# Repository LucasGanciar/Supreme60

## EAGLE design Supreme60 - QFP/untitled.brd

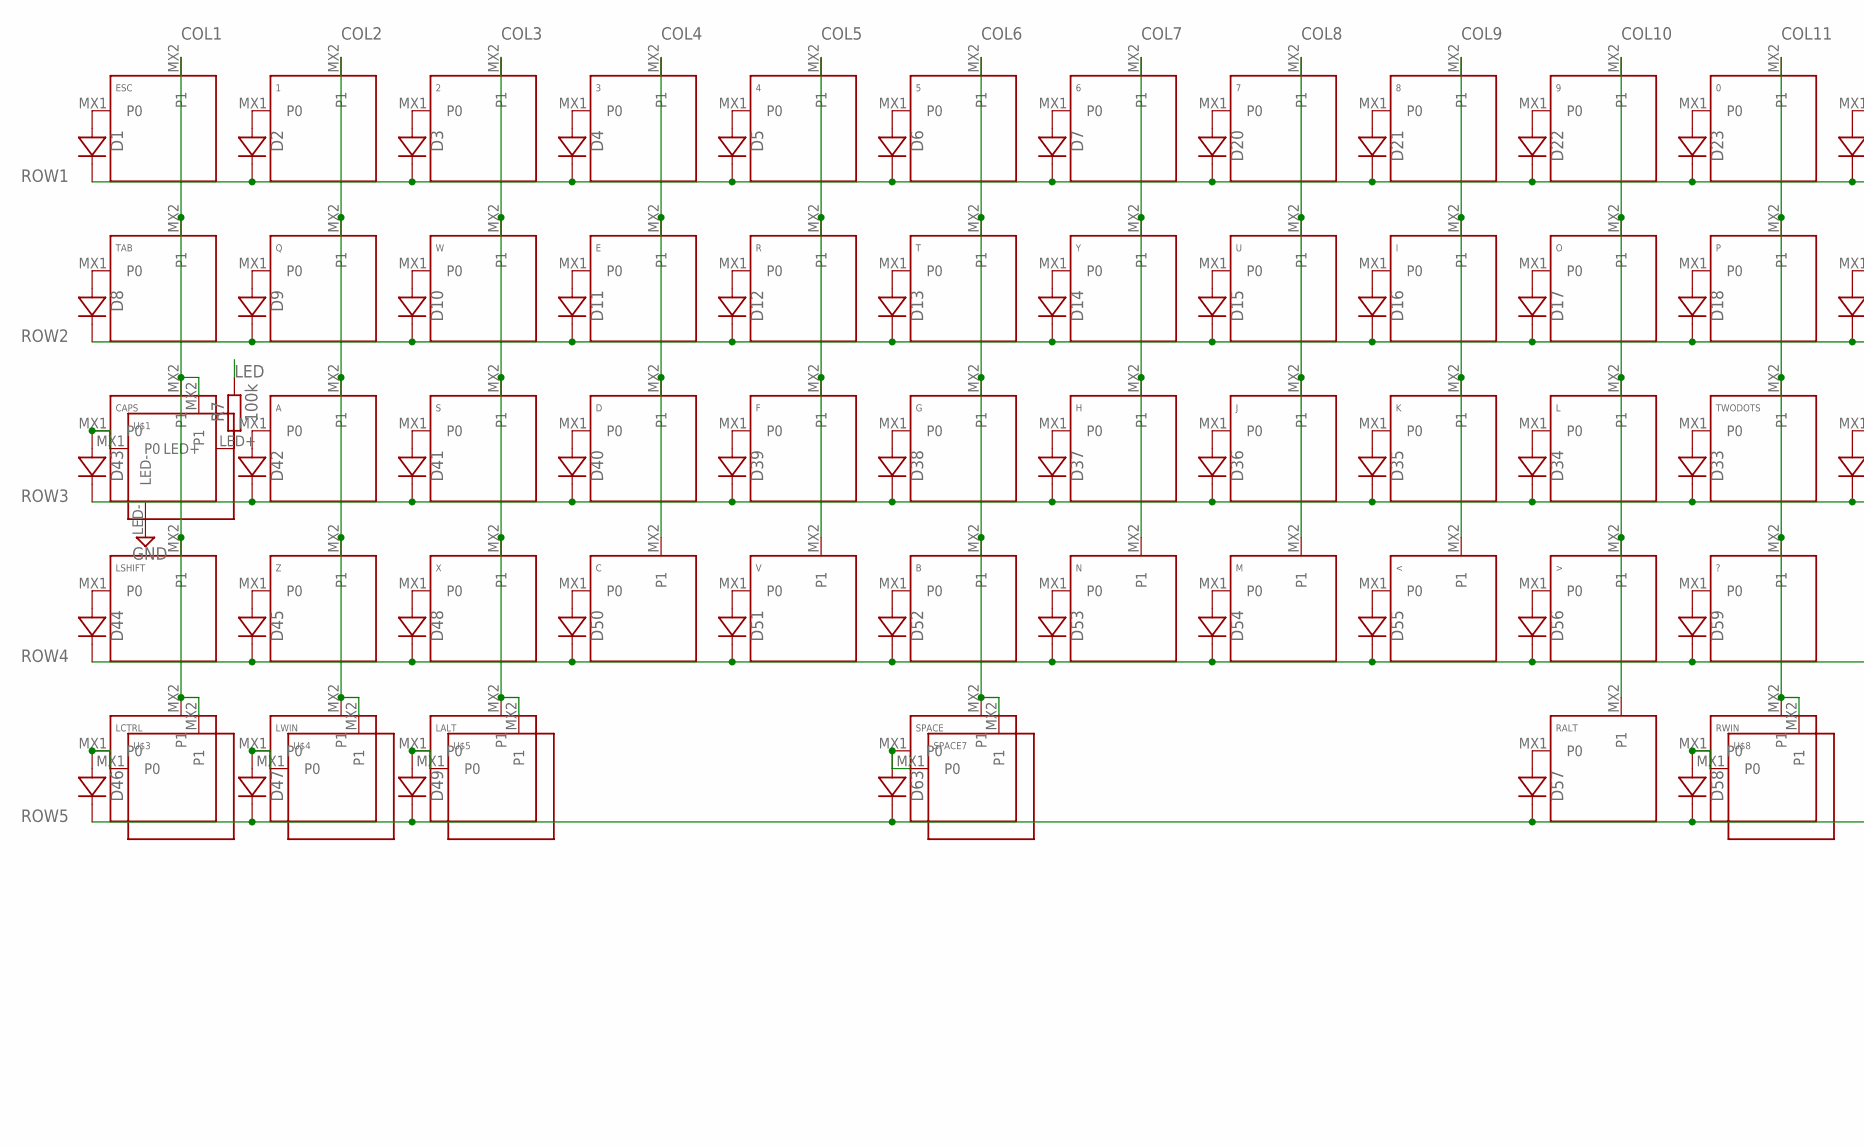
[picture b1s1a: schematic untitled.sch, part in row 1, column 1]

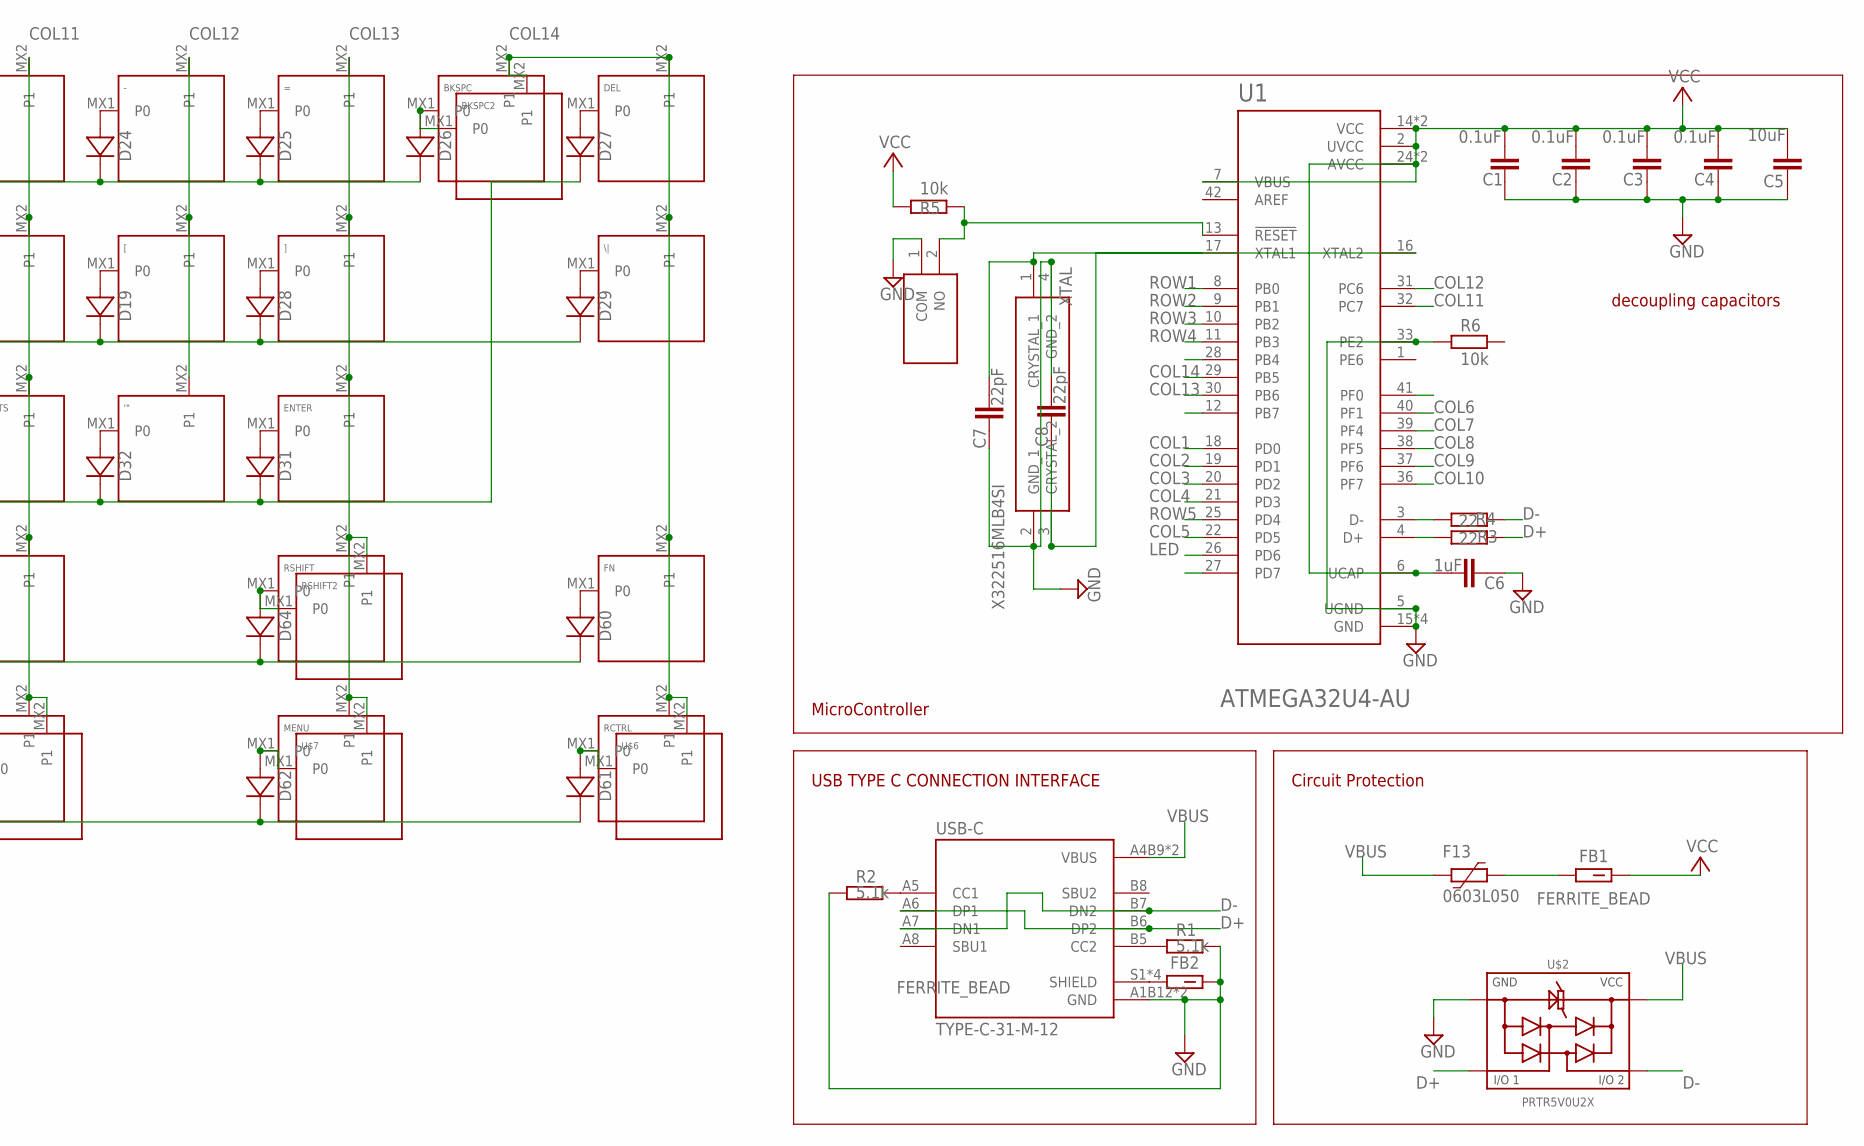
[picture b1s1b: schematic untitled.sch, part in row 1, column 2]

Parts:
0, 1, 2, 3, 4, 5, 6, 7, 8, 9: KEYSWITCH-PLAIN-MX-1U; MX-1U
'": KEYSWITCH-PLAIN-MX-1U; MX-1U
-: KEYSWITCH-PLAIN-MX-1U; MX-1U
<: KEYSWITCH-PLAIN-MX-1U; MX-1U
=: KEYSWITCH-PLAIN-MX-1U; MX-1U
>: KEYSWITCH-PLAIN-MX-1U; MX-1U
?: KEYSWITCH-PLAIN-MX-1U; MX-1U
A: KEYSWITCH-PLAIN-MX-1U; MX-1U
B: KEYSWITCH-PLAIN-MX-1U; MX-1U
BKSPC: KEYSWITCH-PLAIN-MX-1U; MX-1U
BKSPC2: KEYSWITCH-PLAIN-MX-2U; MX-2U
C: KEYSWITCH-PLAIN-MX-1U; MX-1U
C1, C2, C3, C4: 0.1uF; C0603
C5: 10uF; C0603
C6: 1uF; C0603
C7, C8: 22pF; C0603
CAPS: KEYSWITCH-LED-MX-1U-LED; MX-1U-LED
D: KEYSWITCH-PLAIN-MX-1U; MX-1U
D1, D2, D3, D4, D5, D6, D7, D8, D9, D10, D11, D12, D13, D14, D15, D16, D17, D18, D19, D20, D21, D22, D23, D24, D25, D26, D27, D28, D29, D31, D32, D33, D34, D35, D36, D37, D38, D39, D40, D41, D42, D43, D44, D45, D46, D47, D48, D49, D50, D51, D52, D53, D54, D55, D56, D57, D58, D59, D60, D61, D62, D63, D64: DIODE-SOD-123; SOD-123
DEL: KEYSWITCH-PLAIN-MX-1U; MX-1U
E: KEYSWITCH-PLAIN-MX-1U; MX-1U
ENTER: KEYSWITCH-PLAIN-MX-2U; MX-2U
ESC: KEYSWITCH-PLAIN-MX-1U; MX-1U
F: KEYSWITCH-PLAIN-MX-1U; MX-1U
F13: 0603L050; 0603L
FB1, FB2: FERRITE_BEAD; BEADC1608X95N
FN: KEYSWITCH-PLAIN-MX-1U; MX-1U
G: KEYSWITCH-PLAIN-MX-1U; MX-1U
H: KEYSWITCH-PLAIN-MX-1U; MX-1U
I: KEYSWITCH-PLAIN-MX-1U; MX-1U
J: KEYSWITCH-PLAIN-MX-1U; MX-1U
K: KEYSWITCH-PLAIN-MX-1U; MX-1U
L: KEYSWITCH-PLAIN-MX-1U; MX-1U
LALT: KEYSWITCH-PLAIN-MX-1U; MX-1U
LCTRL: KEYSWITCH-PLAIN-MX-1U; MX-1U
LSHIFT: KEYSWITCH-PLAIN-MX-2U; MX-2U
LWIN: KEYSWITCH-PLAIN-MX-1U; MX-1U
M: KEYSWITCH-PLAIN-MX-1U; MX-1U
MENU: KEYSWITCH-PLAIN-MX-1U; MX-1U
N: KEYSWITCH-PLAIN-MX-1U; MX-1U
O: KEYSWITCH-PLAIN-MX-1U; MX-1U
P: KEYSWITCH-PLAIN-MX-1U; MX-1U
Q: KEYSWITCH-PLAIN-MX-1U; MX-1U
R: KEYSWITCH-PLAIN-MX-1U; MX-1U
R1, R2: 5.1k; R0603
R3, R4: 22; R0603
R5, R6: 10k; R0603
R7: 100k; R0603
RALT: KEYSWITCH-PLAIN-MX-1U; MX-1U
RCTRL: KEYSWITCH-PLAIN-MX-1U; MX-1U
RSHIFT: KEYSWITCH-PLAIN-MX-1U; MX-1U
RSHIFT2: KEYSWITCH-PLAIN-MX-2U; MX-2U
RWIN: KEYSWITCH-PLAIN-MX-1U; MX-1U
S: KEYSWITCH-PLAIN-MX-1U; MX-1U
S1: EVP-AWBD2A; EVPAWBD4A
SPACE: KEYSWITCH-PLAIN-MX-6.25U-FLIPPED; MX-6.25U-FLIPPED
SPACE7: KEYSWITCH-PLAIN-MX-7U-FLIPPED; MX-7U-FLIPPED
T: KEYSWITCH-PLAIN-MX-1U; MX-1U
TAB: KEYSWITCH-PLAIN-MX-1U; MX-1U
TWODOTS: KEYSWITCH-PLAIN-MX-1U; MX-1U
U: KEYSWITCH-PLAIN-MX-1U; MX-1U
U1: ATMEGA32U4-AU; QFP80P1200X1200X120-44N
U$1, U$3, U$4, U$5, U$6, U$7, U$8: KEYSWITCH-PLAIN-MX-1U; MX-1U
U$2: PRTR5V0U2X
USB-C: TYPE-C-31-M-12; HRO_TYPE-C-31-M-12
V: KEYSWITCH-PLAIN-MX-1U; MX-1U
W: KEYSWITCH-PLAIN-MX-1U; MX-1U
X: KEYSWITCH-PLAIN-MX-1U; MX-1U
XTAL: X322516MLB4SI
Y: KEYSWITCH-PLAIN-MX-1U; MX-1U
Z: KEYSWITCH-PLAIN-MX-1U; MX-1U
[: KEYSWITCH-PLAIN-MX-1U; MX-1U
\|: KEYSWITCH-PLAIN-MX-1U; MX-1U
]: KEYSWITCH-PLAIN-MX-1U; MX-1U

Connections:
COL1: CAPS.MX2 (P1), ESC.MX2 (P1), LCTRL.MX2 (P1), LSHIFT.MX2 (P1), TAB.MX2 (P1), U1.18 (PD0), U$1.MX2 (P1), U$3.MX2 (P1)
COL2: 1.MX2 (P1), A.MX2 (P1), LWIN.MX2 (P1), Q.MX2 (P1), U1.19 (PD1), U$4.MX2 (P1), Z.MX2 (P1)
COL3: 2.MX2 (P1), LALT.MX2 (P1), S.MX2 (P1), U1.20 (PD2), U$5.MX2 (P1), W.MX2 (P1), X.MX2 (P1)
COL4: 3.MX2 (P1), C.MX2 (P1), D.MX2 (P1), E.MX2 (P1), U1.21 (PD3)
COL5: 4.MX2 (P1), F.MX2 (P1), R.MX2 (P1), U1.22 (PD5), V.MX2 (P1)
COL6: 5.MX2 (P1), B.MX2 (P1), G.MX2 (P1), SPACE.MX2 (P1), SPACE7.MX2 (P1), T.MX2 (P1), U1.40 (PF1)
COL7: 6.MX2 (P1), H.MX2 (P1), N.MX2 (P1), U1.39 (PF4), Y.MX2 (P1)
COL8: 7.MX2 (P1), J.MX2 (P1), M.MX2 (P1), U.MX2 (P1), U1.38 (PF5)
COL9: 8.MX2 (P1), <.MX2 (P1), I.MX2 (P1), K.MX2 (P1), U1.37 (PF6)
COL10: 9.MX2 (P1), >.MX2 (P1), L.MX2 (P1), O.MX2 (P1), RALT.MX2 (P1), U1.36 (PF7)
COL11: 0.MX2 (P1), ?.MX2 (P1), P.MX2 (P1), RWIN.MX2 (P1), TWODOTS.MX2 (P1), U1.32 (PC7), U$8.MX2 (P1)
COL12: '".MX2 (P1), -.MX2 (P1), U1.31 (PC6), [.MX2 (P1)
COL13: =.MX2 (P1), ENTER.MX2 (P1), MENU.MX2 (P1), RSHIFT.MX2 (P1), RSHIFT2.MX2 (P1), U1.30 (PB6), U$7.MX2 (P1), ].MX2 (P1)
COL14: BKSPC.MX2 (P1), BKSPC2.MX2 (P1), DEL.MX2 (P1), FN.MX2 (P1), RCTRL.MX2 (P1), U1.29 (PB5), U$6.MX2 (P1), \|.MX2 (P1)
D+: R4.1, U$2.2, USB-C.A6 (DP1), USB-C.B6 (DP2)
D-: R3.1, U$2.3, USB-C.A7 (DN1), USB-C.B7 (DN2)
GND: C1.1, C2.1, C3.1, C4.1, C5.1, C6.1, C7.1, C8.2, CAPS.LED-, FB2.2, R1.2, R2.1, R6.1, S1.1 (COM), U1.5 (UGND), U1.15 (GND), U1.23 (GND), U1.33 (PE2), U1.35 (GND), U1.43 (GND), U$2.1, USB-C.A1B12 (GND), USB-C.B1A12 (GND), XTAL.2 (GND_1), XTAL.4 (GND_2)
LED: R7.2, U1.26 (PD6)
unnamed: D1.A, ESC.MX1 (P0)
unnamed: 1.MX1 (P0), D2.A
unnamed: 2.MX1 (P0), D3.A
unnamed: 3.MX1 (P0), D4.A
unnamed: 4.MX1 (P0), D5.A
unnamed: 5.MX1 (P0), D6.A
unnamed: 6.MX1 (P0), D7.A
unnamed: D8.A, TAB.MX1 (P0)
unnamed: D9.A, Q.MX1 (P0)
unnamed: D10.A, W.MX1 (P0)
unnamed: D11.A, E.MX1 (P0)
unnamed: D12.A, R.MX1 (P0)
unnamed: D13.A, T.MX1 (P0)
unnamed: D14.A, Y.MX1 (P0)
unnamed: D15.A, U.MX1 (P0)
unnamed: D16.A, I.MX1 (P0)
unnamed: D17.A, O.MX1 (P0)
unnamed: D18.A, P.MX1 (P0)
unnamed: D19.A, [.MX1 (P0)
unnamed: 7.MX1 (P0), D20.A
unnamed: 8.MX1 (P0), D21.A
unnamed: 9.MX1 (P0), D22.A
unnamed: 0.MX1 (P0), D23.A
unnamed: -.MX1 (P0), D24.A
unnamed: =.MX1 (P0), D25.A
unnamed: BKSPC.MX1 (P0), BKSPC2.MX1 (P0), D26.A
unnamed: D27.A, DEL.MX1 (P0)
unnamed: D28.A, ].MX1 (P0)
unnamed: D29.A, \|.MX1 (P0)
unnamed: C7.2, U1.17 (XTAL1), XTAL.1 (CRYSTAL_1)
unnamed: D31.A, ENTER.MX1 (P0)
unnamed: '".MX1 (P0), D32.A
unnamed: D33.A, TWODOTS.MX1 (P0)
unnamed: D34.A, L.MX1 (P0)
unnamed: D35.A, K.MX1 (P0)
unnamed: D36.A, J.MX1 (P0)
unnamed: D37.A, H.MX1 (P0)
unnamed: D38.A, G.MX1 (P0)
unnamed: D39.A, F.MX1 (P0)
unnamed: D.MX1 (P0), D40.A
unnamed: D41.A, S.MX1 (P0)
unnamed: A.MX1 (P0), D42.A
unnamed: CAPS.MX1 (P0), D43.A, U$1.MX1 (P0)
unnamed: D44.A, LSHIFT.MX1 (P0)
unnamed: D45.A, Z.MX1 (P0)
unnamed: D46.A, LCTRL.MX1 (P0), U$3.MX1 (P0)
unnamed: D47.A, LWIN.MX1 (P0), U$4.MX1 (P0)
unnamed: D48.A, X.MX1 (P0)
unnamed: D49.A, LALT.MX1 (P0), U$5.MX1 (P0)
unnamed: C.MX1 (P0), D50.A
unnamed: D51.A, V.MX1 (P0)
unnamed: B.MX1 (P0), D52.A
unnamed: D53.A, N.MX1 (P0)
unnamed: D54.A, M.MX1 (P0)
unnamed: <.MX1 (P0), D55.A
unnamed: >.MX1 (P0), D56.A
unnamed: D57.A, RALT.MX1 (P0)
unnamed: D58.A, RWIN.MX1 (P0), U$8.MX1 (P0)
unnamed: ?.MX1 (P0), D59.A
unnamed: D60.A, FN.MX1 (P0)
unnamed: D61.A, RCTRL.MX1 (P0), U$6.MX1 (P0)
unnamed: D62.A, MENU.MX1 (P0), U$7.MX1 (P0)
unnamed: D63.A, SPACE.MX1 (P0), SPACE7.MX1 (P0)
unnamed: D64.A, RSHIFT.MX1 (P0), RSHIFT2.MX1 (P0)
unnamed: C8.1, U1.16 (XTAL2), XTAL.3 (CRYSTAL_2)
unnamed: R5.2, S1.2 (NO), U1.13 (!RESET)
unnamed: CAPS.LED+, R7.1
unnamed: R3.2, U1.3 (D-)
unnamed: R4.2, U1.4 (D+)
unnamed: R1.1, USB-C.B5 (CC2)
unnamed: R2.2, USB-C.A5 (CC1)
unnamed: F13.1, FB1.1
unnamed: FB2.1, USB-C.S1 (SHIELD), USB-C.S2 (SHIELD), USB-C.S3 (SHIELD), USB-C.S4 (SHIELD)
ROW1: D1.C, D2.C, D3.C, D4.C, D5.C, D6.C, D7.C, D20.C, D21.C, D22.C, D23.C, D24.C, D25.C, D26.C, U1.8 (PB0)
ROW2: D8.C, D9.C, D10.C, D11.C, D12.C, D13.C, D14.C, D15.C, D16.C, D17.C, D18.C, D19.C, D28.C, D29.C, U1.9 (PB1)
ROW3: D27.C, D31.C, D32.C, D33.C, D34.C, D35.C, D36.C, D37.C, D38.C, D39.C, D40.C, D41.C, D42.C, D43.C, U1.10 (PB2)
ROW4: D44.C, D45.C, D48.C, D50.C, D51.C, D52.C, D53.C, D54.C, D55.C, D56.C, D59.C, D60.C, D64.C, U1.11 (PB3)
ROW5: D46.C, D47.C, D49.C, D57.C, D58.C, D61.C, D62.C, D63.C, U1.25 (PD4)
VBUS: F13.2, U$2.4, USB-C.A4B9 (VBUS), USB-C.B4A9 (VBUS)
VCC: C1.2, C2.2, C3.2, C4.2, C5.2, C6.2, FB1.2, R5.1, U1.2 (UVCC), U1.6 (UCAP), U1.7 (VBUS), U1.14 (VCC), U1.24 (AVCC), U1.34 (VCC), U1.44 (AVCC)

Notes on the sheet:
USB TYPE C CONNECTION INTERFACE
decoupling capacitors
MicroController
Circuit Protection

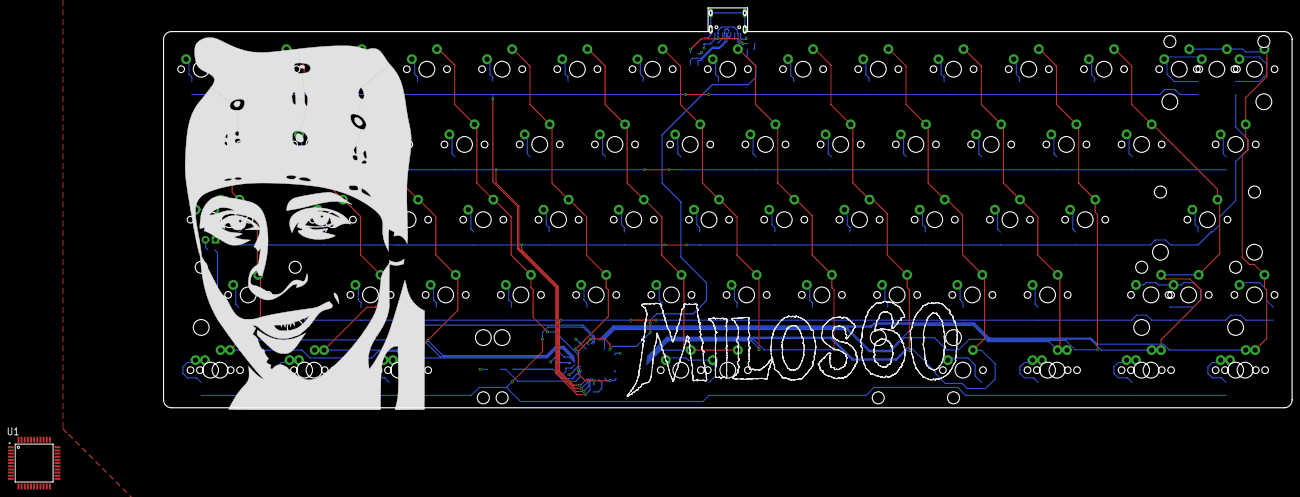
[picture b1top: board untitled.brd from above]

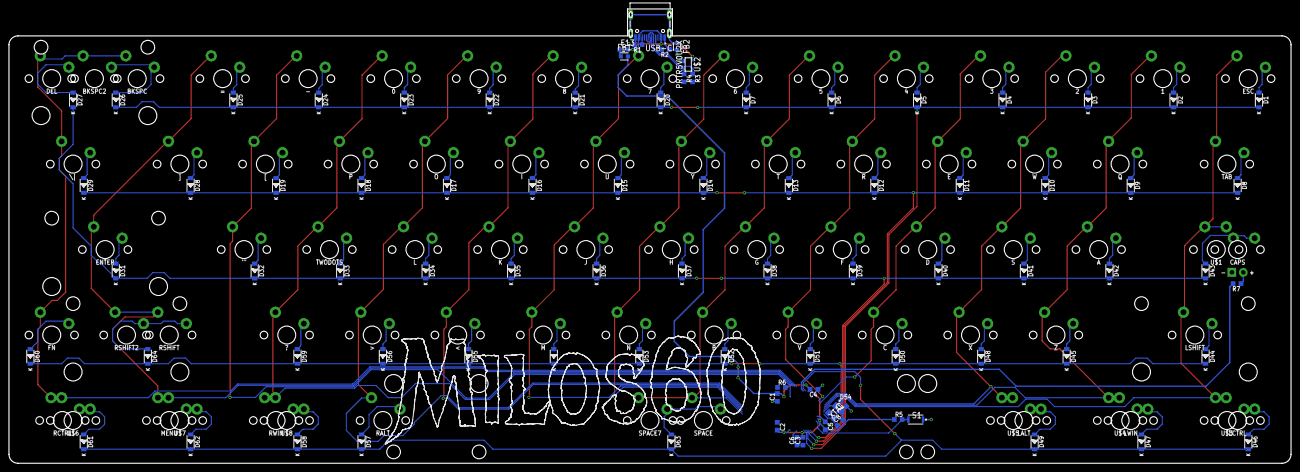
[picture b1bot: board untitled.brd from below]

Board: 2 copper layers, 285.7 x 101.2 mm, 159 parts (85 on the bottom side), 98 nets.
